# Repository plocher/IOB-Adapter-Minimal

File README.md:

# IOB-Adapter-Minimal
## License: CERN Open Hardware Licence v1.2

IOB Adapter - minimal pass through

Simple, low cost, does nothing but pass through signals from Expander to IO Connector

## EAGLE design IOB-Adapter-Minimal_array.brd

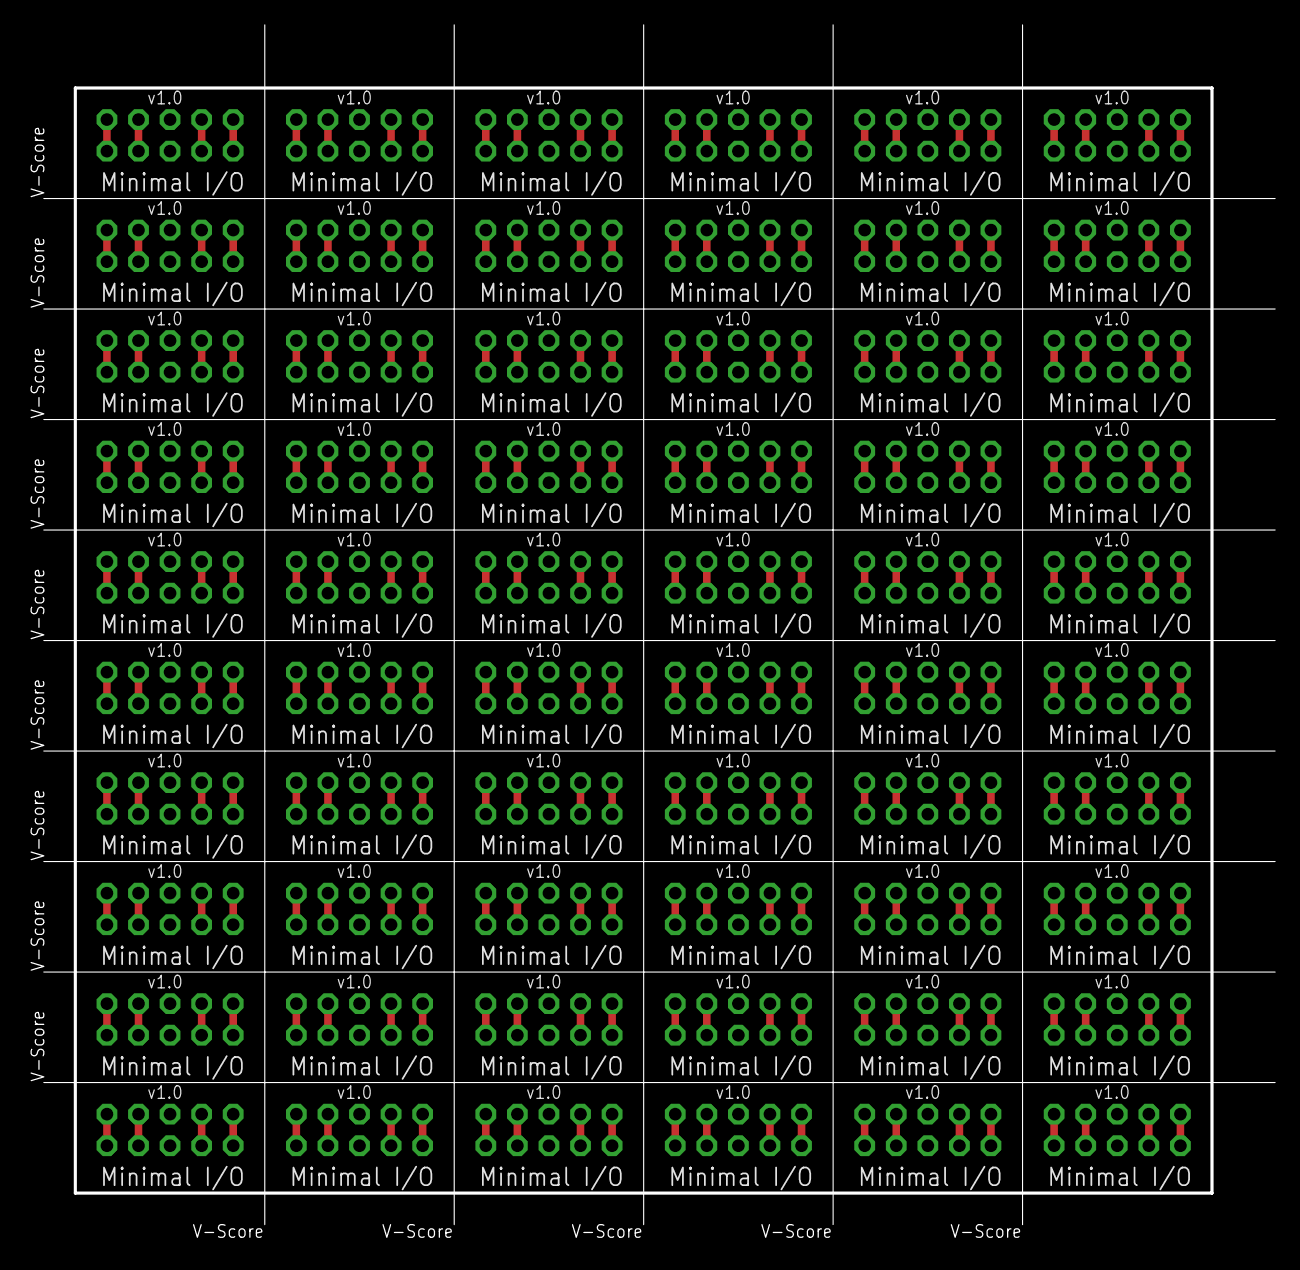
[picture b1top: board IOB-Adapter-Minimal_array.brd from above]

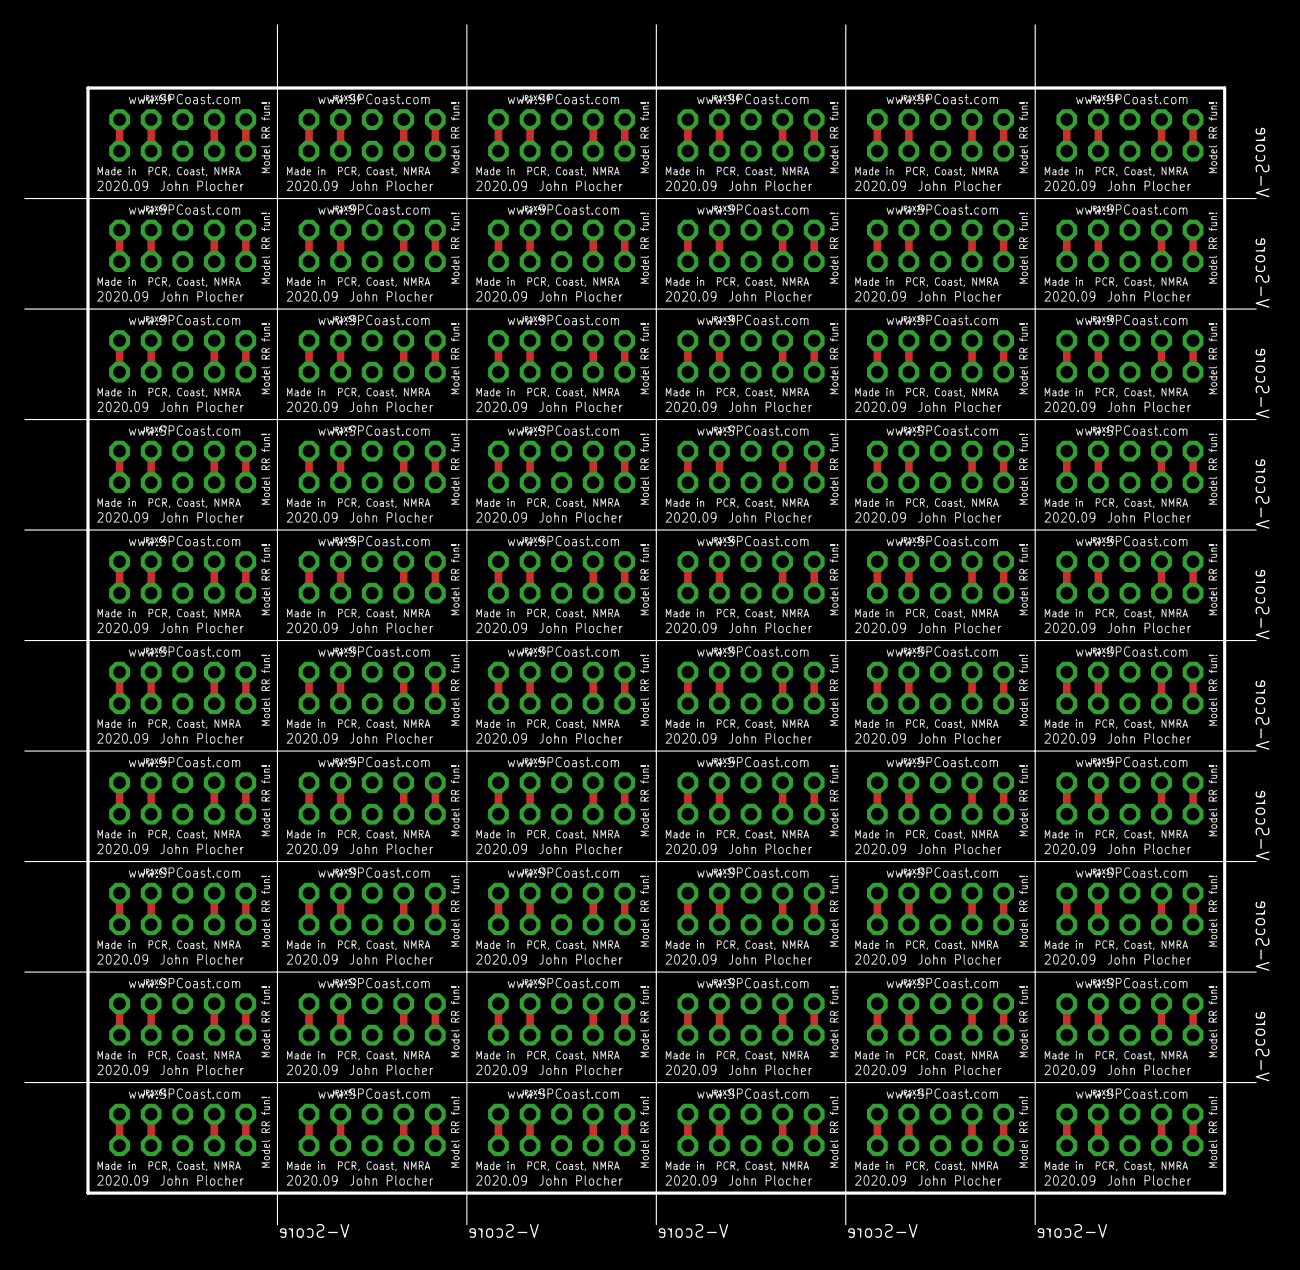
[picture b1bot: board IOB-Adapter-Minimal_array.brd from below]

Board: 2 copper layers, 100.3 x 97.9 mm, 60 parts (60 on the bottom side), 240 nets.

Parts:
JP1X11, JP1X12, JP1X13, JP1X14, JP1X15, JP1X16, JP1X17, JP1X18, JP1X19, JP1X21, JP1X22, JP1X23, JP1X24, JP1X25, JP1X26, JP1X27, JP1X28, JP1X29, JP1X31, JP1X32, JP1X33, JP1X34, JP1X35, JP1X36, JP1X37, JP1X38, JP1X39, JP1X41, JP1X42, JP1X43, JP1X44, JP1X45, JP1X46, JP1X47, JP1X48, JP1X49, JP1X51, JP1X52, JP1X53, JP1X54, JP1X55, JP1X56, JP1X57, JP1X58, JP1X59, JP1X61, JP1X62, JP1X63, JP1X64, JP1X65, JP1X66, JP1X67, JP1X68, JP1X69, JP1X110, JP1X210, JP1X310, JP1X410, JP1X510, JP1X610: 0.100; 2X5_NOSILK

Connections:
unnamed: JP1X11.1, JP1X11.2
unnamed: JP1X12.1, JP1X12.2
unnamed: JP1X13.1, JP1X13.2
unnamed: JP1X14.1, JP1X14.2
unnamed: JP1X15.1, JP1X15.2
unnamed: JP1X16.1, JP1X16.2
unnamed: JP1X17.1, JP1X17.2
unnamed: JP1X18.1, JP1X18.2
unnamed: JP1X19.1, JP1X19.2
unnamed: JP1X21.1, JP1X21.2
unnamed: JP1X22.1, JP1X22.2
unnamed: JP1X23.1, JP1X23.2
unnamed: JP1X24.1, JP1X24.2
unnamed: JP1X25.1, JP1X25.2
unnamed: JP1X26.1, JP1X26.2
unnamed: JP1X27.1, JP1X27.2
unnamed: JP1X28.1, JP1X28.2
unnamed: JP1X29.1, JP1X29.2
unnamed: JP1X31.1, JP1X31.2
unnamed: JP1X32.1, JP1X32.2
unnamed: JP1X33.1, JP1X33.2
unnamed: JP1X34.1, JP1X34.2
unnamed: JP1X35.1, JP1X35.2
unnamed: JP1X36.1, JP1X36.2
unnamed: JP1X37.1, JP1X37.2
unnamed: JP1X38.1, JP1X38.2
unnamed: JP1X39.1, JP1X39.2
unnamed: JP1X41.1, JP1X41.2
unnamed: JP1X42.1, JP1X42.2
unnamed: JP1X43.1, JP1X43.2
unnamed: JP1X44.1, JP1X44.2
unnamed: JP1X45.1, JP1X45.2
unnamed: JP1X46.1, JP1X46.2
unnamed: JP1X47.1, JP1X47.2
unnamed: JP1X48.1, JP1X48.2
unnamed: JP1X49.1, JP1X49.2
unnamed: JP1X51.1, JP1X51.2
unnamed: JP1X52.1, JP1X52.2
unnamed: JP1X53.1, JP1X53.2
unnamed: JP1X54.1, JP1X54.2
unnamed: JP1X55.1, JP1X55.2
unnamed: JP1X56.1, JP1X56.2
unnamed: JP1X57.1, JP1X57.2
unnamed: JP1X58.1, JP1X58.2
unnamed: JP1X59.1, JP1X59.2
unnamed: JP1X61.1, JP1X61.2
unnamed: JP1X62.1, JP1X62.2
unnamed: JP1X63.1, JP1X63.2
unnamed: JP1X64.1, JP1X64.2
unnamed: JP1X65.1, JP1X65.2
unnamed: JP1X66.1, JP1X66.2
unnamed: JP1X67.1, JP1X67.2
unnamed: JP1X68.1, JP1X68.2
unnamed: JP1X69.1, JP1X69.2
unnamed: JP1X110.1, JP1X110.2
unnamed: JP1X210.1, JP1X210.2
unnamed: JP1X310.1, JP1X310.2
unnamed: JP1X410.1, JP1X410.2
unnamed: JP1X510.1, JP1X510.2
unnamed: JP1X610.1, JP1X610.2
unnamed: JP1X11.3, JP1X11.4
unnamed: JP1X12.3, JP1X12.4
unnamed: JP1X13.3, JP1X13.4
unnamed: JP1X14.3, JP1X14.4
unnamed: JP1X15.3, JP1X15.4
unnamed: JP1X16.3, JP1X16.4
unnamed: JP1X17.3, JP1X17.4
unnamed: JP1X18.3, JP1X18.4
unnamed: JP1X19.3, JP1X19.4
unnamed: JP1X21.3, JP1X21.4
unnamed: JP1X22.3, JP1X22.4
unnamed: JP1X23.3, JP1X23.4
unnamed: JP1X24.3, JP1X24.4
unnamed: JP1X25.3, JP1X25.4
unnamed: JP1X26.3, JP1X26.4
unnamed: JP1X27.3, JP1X27.4
unnamed: JP1X28.3, JP1X28.4
unnamed: JP1X29.3, JP1X29.4
unnamed: JP1X31.3, JP1X31.4
unnamed: JP1X32.3, JP1X32.4
unnamed: JP1X33.3, JP1X33.4
unnamed: JP1X34.3, JP1X34.4
unnamed: JP1X35.3, JP1X35.4
unnamed: JP1X36.3, JP1X36.4
unnamed: JP1X37.3, JP1X37.4
unnamed: JP1X38.3, JP1X38.4
unnamed: JP1X39.3, JP1X39.4
unnamed: JP1X41.3, JP1X41.4
unnamed: JP1X42.3, JP1X42.4
unnamed: JP1X43.3, JP1X43.4
unnamed: JP1X44.3, JP1X44.4
unnamed: JP1X45.3, JP1X45.4
unnamed: JP1X46.3, JP1X46.4
unnamed: JP1X47.3, JP1X47.4
unnamed: JP1X48.3, JP1X48.4
unnamed: JP1X49.3, JP1X49.4
unnamed: JP1X51.3, JP1X51.4
unnamed: JP1X52.3, JP1X52.4
unnamed: JP1X53.3, JP1X53.4
unnamed: JP1X54.3, JP1X54.4
unnamed: JP1X55.3, JP1X55.4
unnamed: JP1X56.3, JP1X56.4
unnamed: JP1X57.3, JP1X57.4
unnamed: JP1X58.3, JP1X58.4
unnamed: JP1X59.3, JP1X59.4
unnamed: JP1X61.3, JP1X61.4
unnamed: JP1X62.3, JP1X62.4
unnamed: JP1X63.3, JP1X63.4
unnamed: JP1X64.3, JP1X64.4
unnamed: JP1X65.3, JP1X65.4
unnamed: JP1X66.3, JP1X66.4
unnamed: JP1X67.3, JP1X67.4
unnamed: JP1X68.3, JP1X68.4
unnamed: JP1X69.3, JP1X69.4
unnamed: JP1X110.3, JP1X110.4
unnamed: JP1X210.3, JP1X210.4
unnamed: JP1X310.3, JP1X310.4
unnamed: JP1X410.3, JP1X410.4
unnamed: JP1X510.3, JP1X510.4
unnamed: JP1X610.3, JP1X610.4
unnamed: JP1X11.7, JP1X11.8
unnamed: JP1X12.7, JP1X12.8
unnamed: JP1X13.7, JP1X13.8
unnamed: JP1X14.7, JP1X14.8
unnamed: JP1X15.7, JP1X15.8
unnamed: JP1X16.7, JP1X16.8
unnamed: JP1X17.7, JP1X17.8
unnamed: JP1X18.7, JP1X18.8
unnamed: JP1X19.7, JP1X19.8
unnamed: JP1X21.7, JP1X21.8
unnamed: JP1X22.7, JP1X22.8
unnamed: JP1X23.7, JP1X23.8
unnamed: JP1X24.7, JP1X24.8
unnamed: JP1X25.7, JP1X25.8
unnamed: JP1X26.7, JP1X26.8
unnamed: JP1X27.7, JP1X27.8
unnamed: JP1X28.7, JP1X28.8
unnamed: JP1X29.7, JP1X29.8
unnamed: JP1X31.7, JP1X31.8
unnamed: JP1X32.7, JP1X32.8
unnamed: JP1X33.7, JP1X33.8
unnamed: JP1X34.7, JP1X34.8
unnamed: JP1X35.7, JP1X35.8
unnamed: JP1X36.7, JP1X36.8
unnamed: JP1X37.7, JP1X37.8
unnamed: JP1X38.7, JP1X38.8
unnamed: JP1X39.7, JP1X39.8
unnamed: JP1X41.7, JP1X41.8
unnamed: JP1X42.7, JP1X42.8
unnamed: JP1X43.7, JP1X43.8
unnamed: JP1X44.7, JP1X44.8
unnamed: JP1X45.7, JP1X45.8
unnamed: JP1X46.7, JP1X46.8
unnamed: JP1X47.7, JP1X47.8
unnamed: JP1X48.7, JP1X48.8
unnamed: JP1X49.7, JP1X49.8
unnamed: JP1X51.7, JP1X51.8
unnamed: JP1X52.7, JP1X52.8
unnamed: JP1X53.7, JP1X53.8
unnamed: JP1X54.7, JP1X54.8
unnamed: JP1X55.7, JP1X55.8
unnamed: JP1X56.7, JP1X56.8
unnamed: JP1X57.7, JP1X57.8
unnamed: JP1X58.7, JP1X58.8
unnamed: JP1X59.7, JP1X59.8
unnamed: JP1X61.7, JP1X61.8
unnamed: JP1X62.7, JP1X62.8
unnamed: JP1X63.7, JP1X63.8
unnamed: JP1X64.7, JP1X64.8
unnamed: JP1X65.7, JP1X65.8
unnamed: JP1X66.7, JP1X66.8
unnamed: JP1X67.7, JP1X67.8
unnamed: JP1X68.7, JP1X68.8
unnamed: JP1X69.7, JP1X69.8
unnamed: JP1X110.7, JP1X110.8
unnamed: JP1X210.7, JP1X210.8
unnamed: JP1X310.7, JP1X310.8
unnamed: JP1X410.7, JP1X410.8
unnamed: JP1X510.7, JP1X510.8
unnamed: JP1X610.7, JP1X610.8
unnamed: JP1X11.9, JP1X11.10
unnamed: JP1X12.9, JP1X12.10
unnamed: JP1X13.9, JP1X13.10
unnamed: JP1X14.9, JP1X14.10
unnamed: JP1X15.9, JP1X15.10
unnamed: JP1X16.9, JP1X16.10
unnamed: JP1X17.9, JP1X17.10
unnamed: JP1X18.9, JP1X18.10
unnamed: JP1X19.9, JP1X19.10
unnamed: JP1X21.9, JP1X21.10
unnamed: JP1X22.9, JP1X22.10
unnamed: JP1X23.9, JP1X23.10
unnamed: JP1X24.9, JP1X24.10
unnamed: JP1X25.9, JP1X25.10
unnamed: JP1X26.9, JP1X26.10
unnamed: JP1X27.9, JP1X27.10
unnamed: JP1X28.9, JP1X28.10
unnamed: JP1X29.9, JP1X29.10
unnamed: JP1X31.9, JP1X31.10
unnamed: JP1X32.9, JP1X32.10
unnamed: JP1X33.9, JP1X33.10
unnamed: JP1X34.9, JP1X34.10
unnamed: JP1X35.9, JP1X35.10
unnamed: JP1X36.9, JP1X36.10
unnamed: JP1X37.9, JP1X37.10
unnamed: JP1X38.9, JP1X38.10
unnamed: JP1X39.9, JP1X39.10
unnamed: JP1X41.9, JP1X41.10
unnamed: JP1X42.9, JP1X42.10
unnamed: JP1X43.9, JP1X43.10
unnamed: JP1X44.9, JP1X44.10
unnamed: JP1X45.9, JP1X45.10
unnamed: JP1X46.9, JP1X46.10
unnamed: JP1X47.9, JP1X47.10
unnamed: JP1X48.9, JP1X48.10
unnamed: JP1X49.9, JP1X49.10
unnamed: JP1X51.9, JP1X51.10
unnamed: JP1X52.9, JP1X52.10
unnamed: JP1X53.9, JP1X53.10
unnamed: JP1X54.9, JP1X54.10
unnamed: JP1X55.9, JP1X55.10
unnamed: JP1X56.9, JP1X56.10
unnamed: JP1X57.9, JP1X57.10
unnamed: JP1X58.9, JP1X58.10
unnamed: JP1X59.9, JP1X59.10
unnamed: JP1X61.9, JP1X61.10
unnamed: JP1X62.9, JP1X62.10
unnamed: JP1X63.9, JP1X63.10
unnamed: JP1X64.9, JP1X64.10
unnamed: JP1X65.9, JP1X65.10
unnamed: JP1X66.9, JP1X66.10
unnamed: JP1X67.9, JP1X67.10
unnamed: JP1X68.9, JP1X68.10
unnamed: JP1X69.9, JP1X69.10
unnamed: JP1X110.9, JP1X110.10
unnamed: JP1X210.9, JP1X210.10
unnamed: JP1X310.9, JP1X310.10
unnamed: JP1X410.9, JP1X410.10
unnamed: JP1X510.9, JP1X510.10
unnamed: JP1X610.9, JP1X610.10

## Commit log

2020-09-18 Initial version
2020-10-06 normalized values
